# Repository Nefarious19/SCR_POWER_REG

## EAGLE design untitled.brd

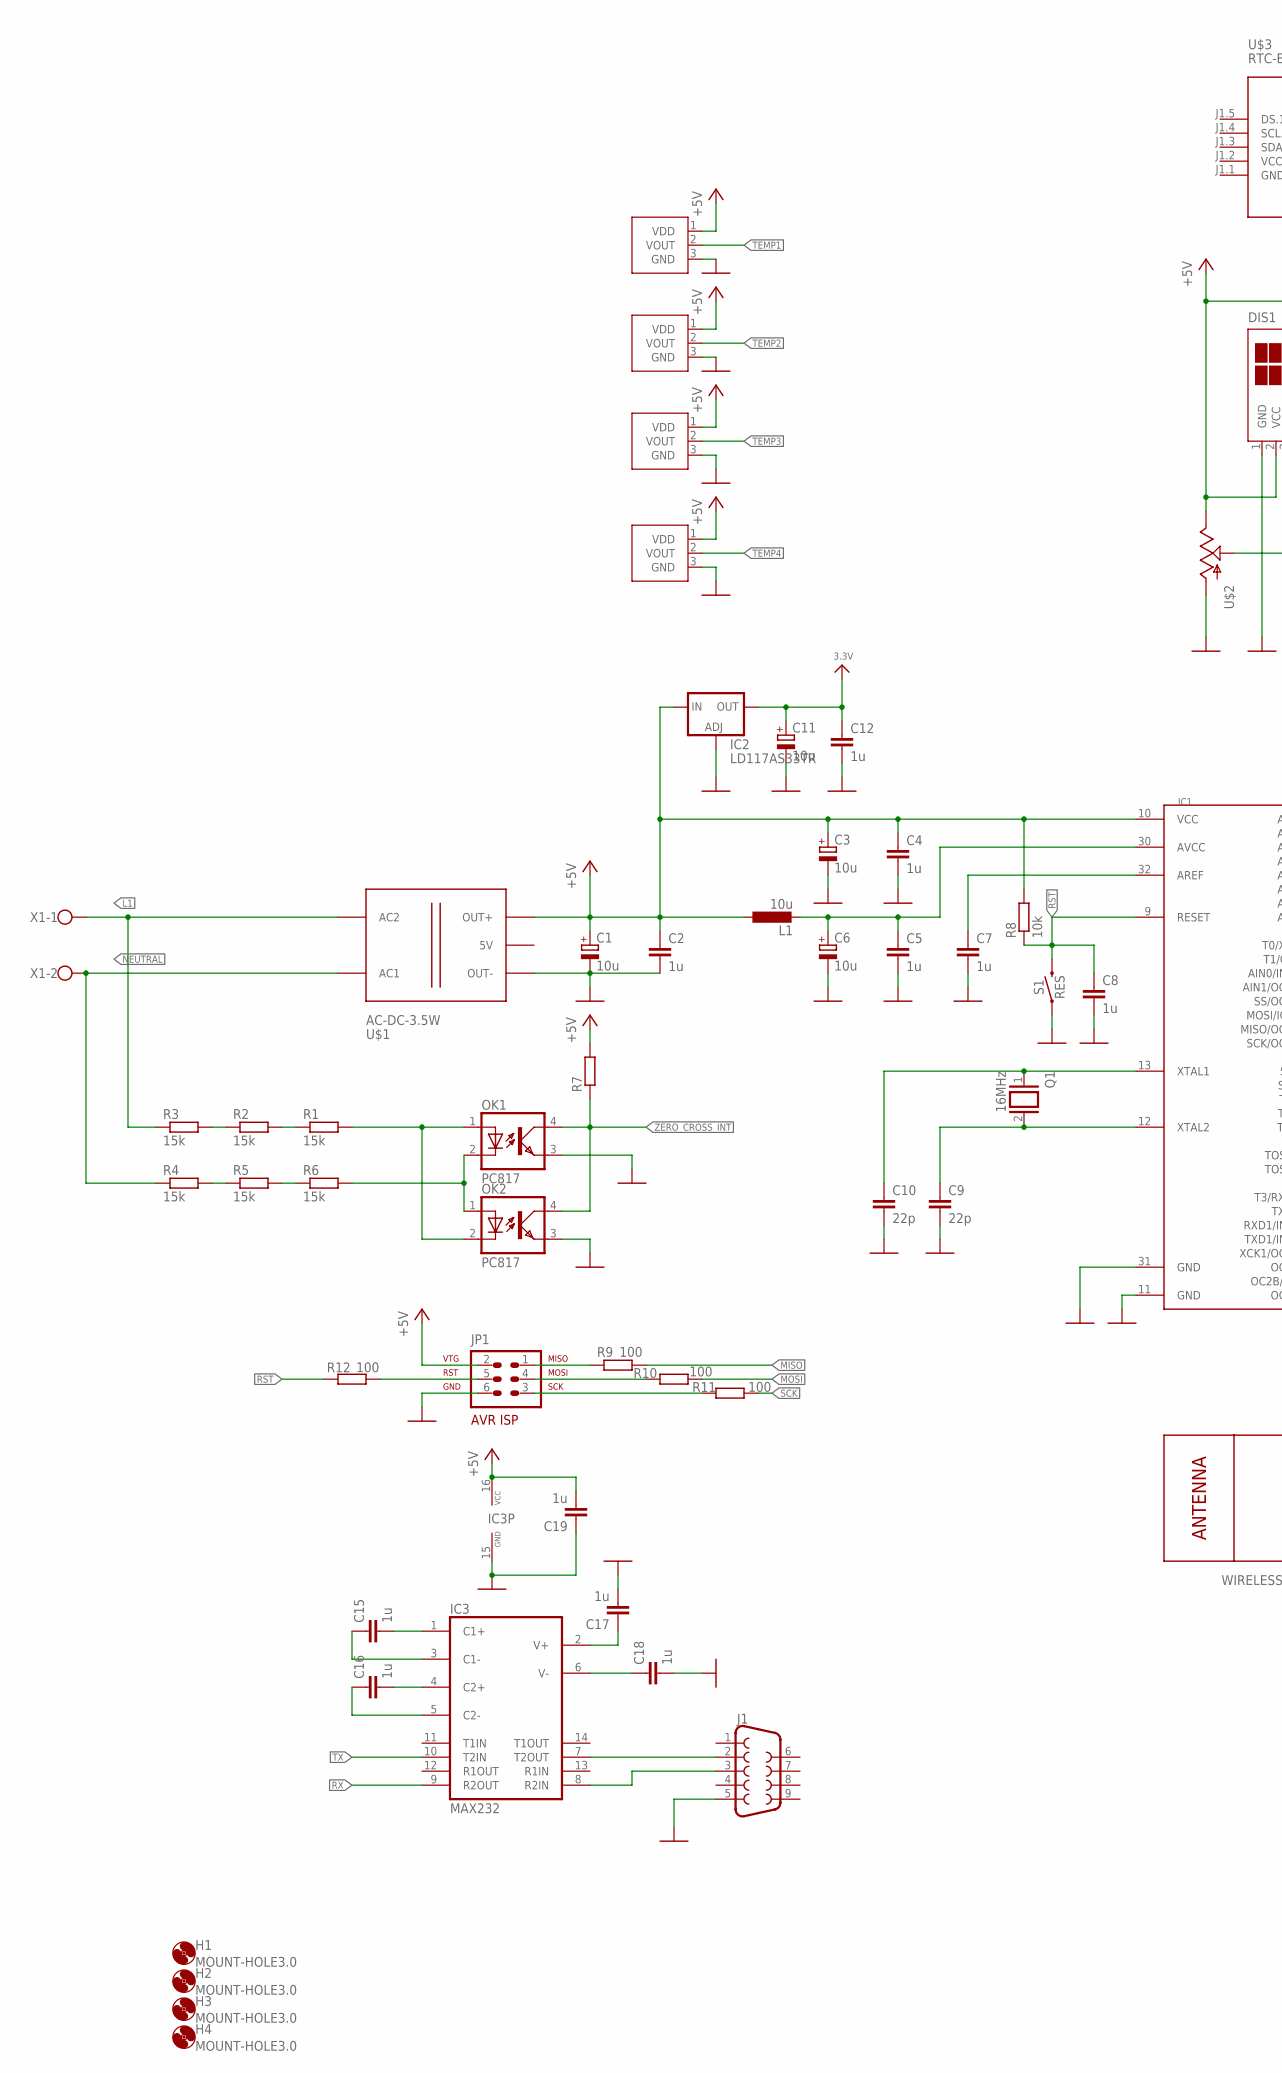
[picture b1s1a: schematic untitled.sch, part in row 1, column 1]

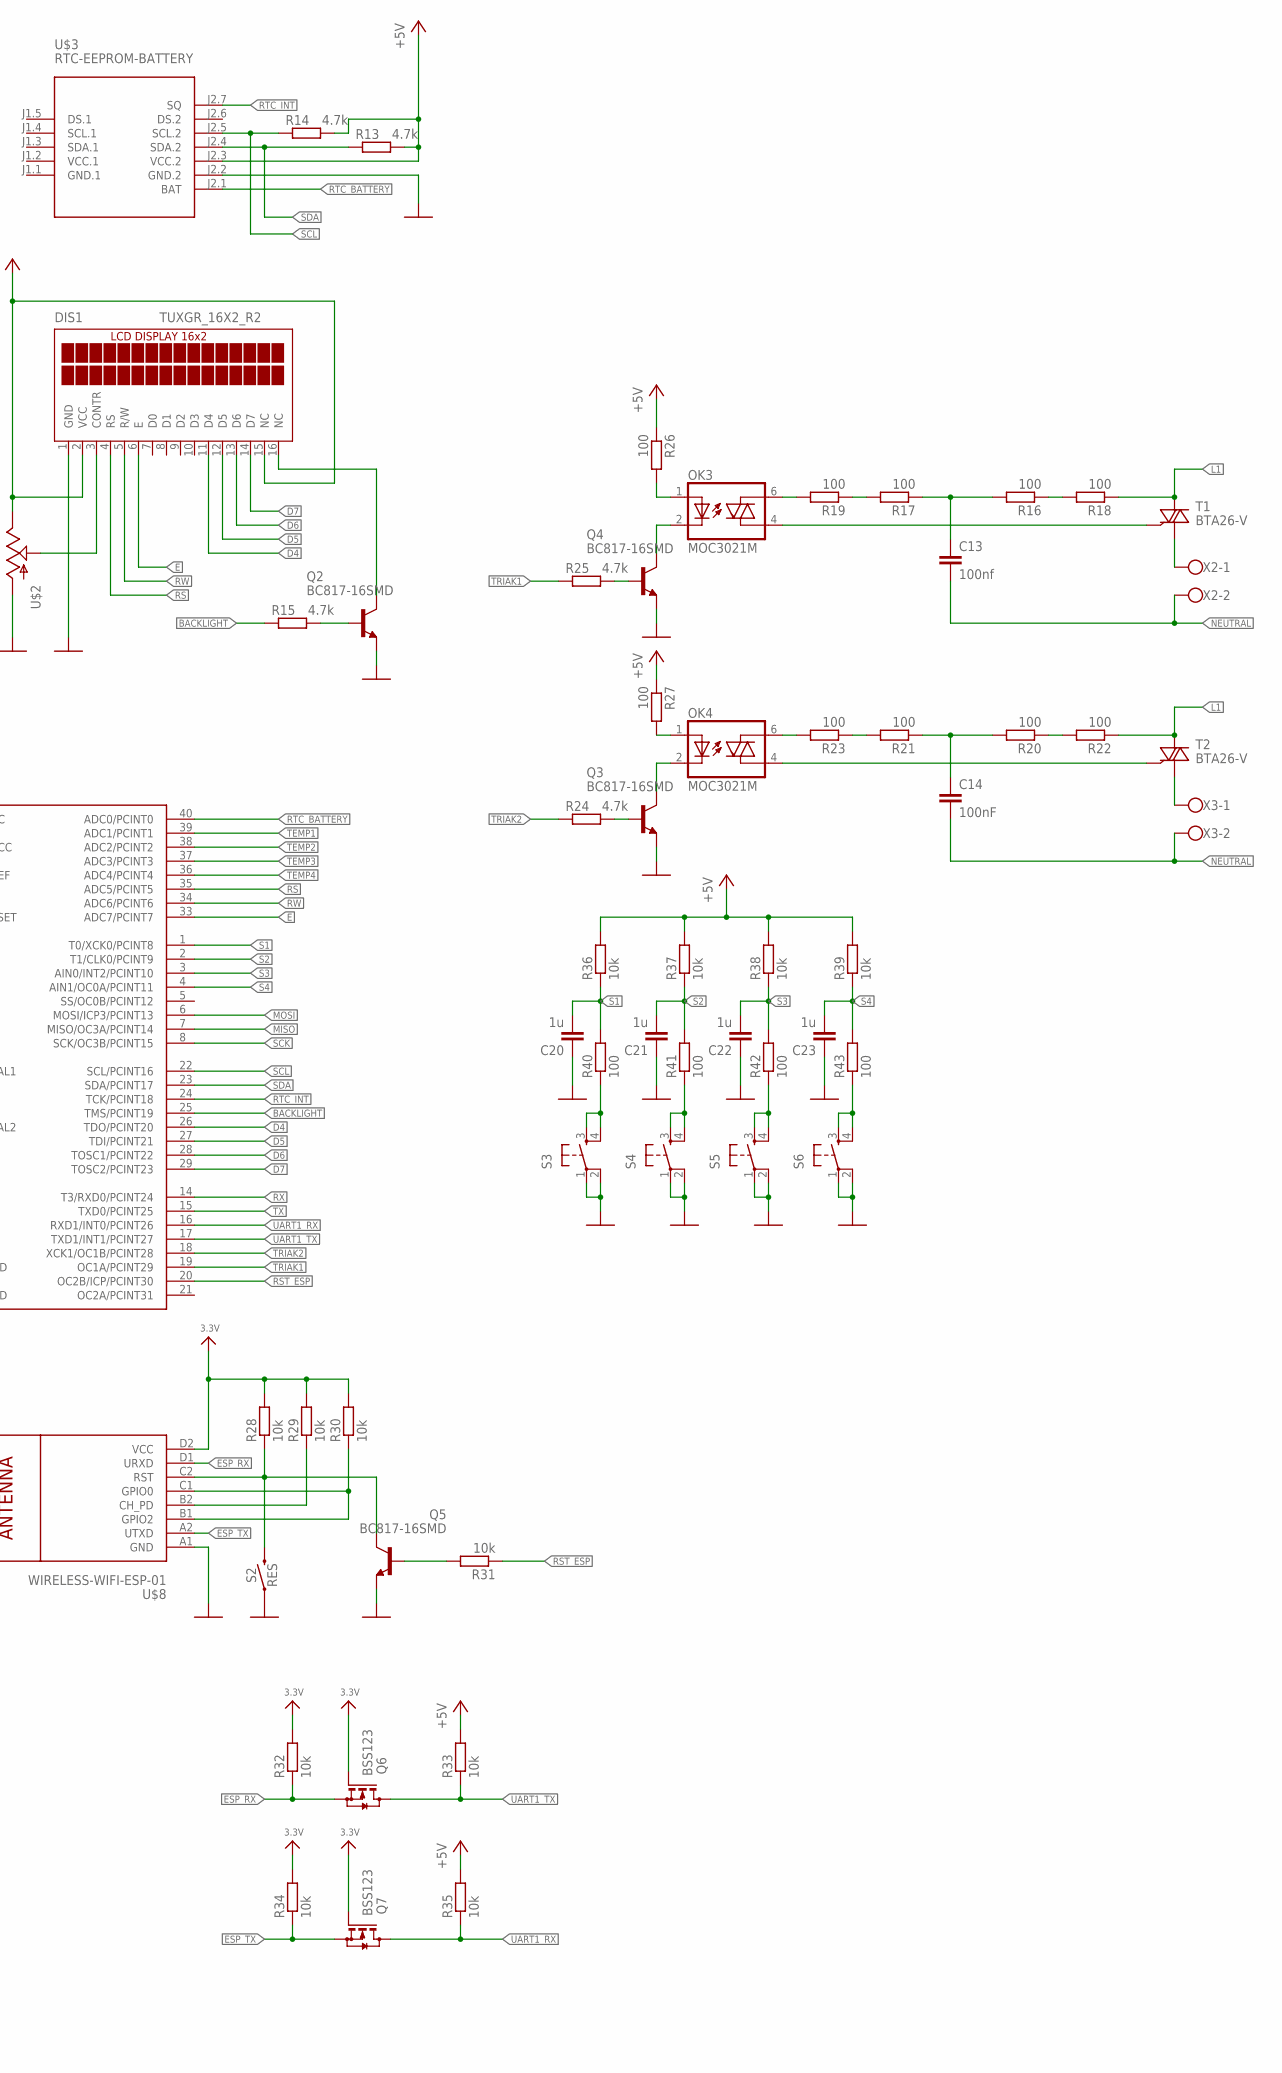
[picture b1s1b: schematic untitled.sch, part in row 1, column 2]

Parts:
C1, C3, C6, C11: 10u; 153CLV-0505
C2, C4, C5, C7, C8, C12, C15, C16, C17, C18, C19, C20, C21, C22, C23: 1u; C1206
C9, C10: 22p; C1206
C13: 100nf; C150-064X183
C14: 100nF; C150-064X183
DIS1: TUXGR_16X2_R2
H1, H2, H3, H4: MOUNT-HOLE3.0; 3,0
IC1: MEGA1284P; DIL40
IC2: LD117AS33TR; SOT223
IC3: MAX232; DIL16
J1: DB9FEMALE; DB9
JP1: AVR-ISP-6
L1: 10u; 0204/5
OK1, OK2: PC817; DIL04
OK3, OK4: MOC3021M; DIL06
Q1: 16MHz; QS
Q2, Q3, Q4, Q5: BC817-16SMD; SOT23-BEC
Q6, Q7: BSS123; SOT23
R1, R2, R3, R4, R5, R6: 15k; M1206
R7: R-EU_M1206; M1206
R8, R28, R29, R30, R31, R32, R33, R34, R35, R36, R37, R38, R39: 10k; M1206
R9, R10, R11, R12, R16, R17, R18, R19, R20, R21, R22, R23, R26, R27, R40, R41, R42, R43: 100; M1206
R13, R14, R15, R24, R25: 4.7k; M1206
S1, S2: RES; TACTILE_SWITCH_SMD_6.0X3.5MM
S3, S4, S5, S6: TAC_SWITCHPTH; TACTILE-PTH
T1, T2: BTA26-V; TOP3S-1
U$1: AC-DC-3.5W
U$2: POTTRIM; TRIM_POT
U$3: RTC-EEPROM-BATTERY
U$4, U$5, U$6, U$7: MCP970XTO; TO92
U$8: WIRELESS-WIFI-ESP-01
X1, X2, X3: AK500/2

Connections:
3.3V: C11.+, C12.1, IC2.4 (OUT), Q6.1 (G), Q7.1 (G), R28.2, R29.2, R30.2, R32.2, R34.2, U$8.D2 (VCC)
+5V: C1.+, C2.1, C3.+, C4.1, C19.2, DIS1.2 (VCC), DIS1.15 (NC), IC1.10 (VCC), IC2.3 (IN), IC3.16 (VCC), JP1.2, L1.1, R7.2, R8.2, R13.2, R14.2, R26.1, R27.1, R33.2, R35.2, R36.2, R37.2, R38.2, R39.2, U$1.J2.3 (OUT+), U$2.2 (E), U$3.J2.3 (VCC.2), U$4.1 (VDD), U$5.1 (VDD), U$6.1 (VDD), U$7.1 (VDD)
BACKLIGHT: IC1.25 (TMS/PCINT19), R15.1
D4: DIS1.11 (D4), IC1.26 (TDO/PCINT20)
D5: DIS1.12 (D5), IC1.27 (TDI/PCINT21)
D6: DIS1.13 (D6), IC1.28 (TOSC1/PCINT22)
D7: DIS1.14 (D7), IC1.29 (TOSC2/PCINT23)
E: DIS1.6 (E), IC1.33 (ADC7/PCINT7)
ESP_RST: Q5.C, R28.1, S2.2, U$8.C2 (RST)
ESP_RX: Q6.2 (S), R32.1, U$8.D1 (URXD)
ESP_TX: Q7.2 (S), R34.1, U$8.A2 (UTXD)
GND: C1.-, C2.2, C3.-, C4.2, C5.2, C6.-, C7.2, C8.2, C9.2, C10.2, C11.-, C12.2, C17.2, C18.2, C19.1, C20.1, C21.1, C22.1, C23.1, DIS1.1 (GND), IC1.11 (GND), IC1.31 (GND), IC2.1 (ADJ), IC3.15 (GND), J1.5, JP1.6, OK1.3 (EMIT), OK2.3 (EMIT), Q2.E, Q3.E, Q4.E, Q5.E, S1.1, S2.1, S3.1, S3.2, S4.1, S4.2, S5.1, S5.2, S6.1, S6.2, U$1.J2.1 (OUT-), U$2.3 (A), U$3.J2.2 (GND.2), U$4.3 (GND), U$5.3 (GND), U$6.3 (GND), U$7.3 (GND), U$8.A1 (GND)
GND.1: U$3.J1.1 (GND.1)
L1: R3.1, R18.1, R22.1, T1.A2, T2.A2, U$1.J1.2 (AC2), X1.1
MISO: IC1.7 (MISO/OC3A/PCINT14), R9.2
MOSI: IC1.6 (MOSI/ICP3/PCINT13), R10.2
unnamed: OK1.2 (C), OK2.1 (A), R6.2
unnamed: OK1.1 (A), OK2.2 (C), R1.2
unnamed: R2.1, R3.2
unnamed: R1.1, R2.2
unnamed: R5.2, R6.1
unnamed: R4.2, R5.1
unnamed: OK3.4 (A1), T1.G
unnamed: T1.A1, X2.1
unnamed: C5.1, C6.+, IC1.30 (AVCC), L1.2
unnamed: JP1.5, R12.2
unnamed: C9.1, IC1.12 (XTAL2), Q1.2
unnamed: C7.1, IC1.32 (AREF)
unnamed: C10.1, IC1.13 (XTAL1), Q1.1
unnamed: JP1.1, R9.1
unnamed: JP1.4, R10.1
unnamed: JP1.3, R11.1
unnamed: Q2.B, R15.2
unnamed: DIS1.3 (CONTR), U$2.1 (S)
unnamed: Q5.B, R31.2
unnamed: OK3.6 (A2), R19.2
unnamed: R17.2, R19.1
unnamed: C13.1, R16.2, R17.1
unnamed: R16.1, R18.2
unnamed: OK4.6 (A2), R23.2
unnamed: R21.2, R23.1
unnamed: C14.1, R20.2, R21.1
unnamed: DIS1.16 (NC), Q2.C
unnamed: R20.1, R22.2
unnamed: OK4.4 (A1), T2.G
unnamed: T2.A1, X3.1
unnamed: OK3.1 (A), R26.2
unnamed: OK3.2 (C), Q4.C
unnamed: OK4.1 (A), R27.2
unnamed: OK4.2 (C), Q3.C
unnamed: Q3.B, R24.2
unnamed: Q4.B, R25.2
unnamed: R29.1, U$8.B2 (CH_PD)
unnamed: R30.1, U$8.B1 (GPIO2), U$8.C1 (GPIO0)
unnamed: C15.2, IC3.1 (C1+)
unnamed: R40.1, S3.3, S3.4
unnamed: C16.2, IC3.4 (C2+)
unnamed: R41.1, S4.3, S4.4
unnamed: C15.1, IC3.3 (C1-)
unnamed: C16.1, IC3.5 (C2-)
unnamed: C17.1, IC3.2 (V+)
unnamed: C18.1, IC3.6 (V-)
unnamed: R42.1, S5.3, S5.4
unnamed: R43.1, S6.3, S6.4
unnamed: IC3.7 (T2OUT), J1.2
unnamed: IC3.8 (R2IN), J1.3
NEUTRAL: C13.2, C14.2, R4.1, U$1.J1.1 (AC1), X1.2, X2.2, X3.2
RS: DIS1.4 (RS), IC1.35 (ADC5/PCINT5)
RST: C8.1, IC1.9 (RESET), R8.1, R12.1, S1.2
RST_ESP: IC1.20 (OC2B/ICP/PCINT30), R31.1
RTC_BATTERY: IC1.40 (ADC0/PCINT0), U$3.J2.1 (BAT)
RTC_INT: IC1.24 (TCK/PCINT18), U$3.J2.7 (SQ)
RW: DIS1.5 (R/W), IC1.34 (ADC6/PCINT6)
RX: IC1.14 (T3/RXD0/PCINT24), IC3.9 (R2OUT)
S1: C20.2, IC1.1 (T0/XCK0/PCINT8), R36.1, R40.2
S2: C21.2, IC1.2 (T1/CLK0/PCINT9), R37.1, R41.2
S3: C22.2, IC1.3 (AIN0/INT2/PCINT10), R38.1, R42.2
S4: C23.2, IC1.4 (AIN1/OC0A/PCINT11), R39.1, R43.2
SCK: IC1.8 (SCK/OC3B/PCINT15), R11.2
SCL: IC1.22 (SCL/PCINT16), R14.1, U$3.J2.5 (SCL.2)
SDA: IC1.23 (SDA/PCINT17), R13.1, U$3.J2.4 (SDA.2)
TEMP1: IC1.39 (ADC1/PCINT1), U$7.2 (VOUT)
TEMP2: IC1.38 (ADC2/PCINT2), U$6.2 (VOUT)
TEMP3: IC1.37 (ADC3/PCINT3), U$5.2 (VOUT)
TEMP4: IC1.36 (ADC4/PCINT4), U$4.2 (VOUT)
TRIAK1: IC1.19 (OC1A/PCINT29), R25.1
TRIAK2: IC1.18 (XCK1/OC1B/PCINT28), R24.1
TX: IC1.15 (TXD0/PCINT25), IC3.10 (T2IN)
UART1_RX: IC1.16 (RXD1/INT0/PCINT26), Q7.3 (D), R35.1
UART1_TX: IC1.17 (TXD1/INT1/PCINT27), Q6.3 (D), R33.1
VCC.1: U$3.J1.2 (VCC.1)
ZERO_CROSS_INT: OK1.4 (COL), OK2.4 (COL), R7.1

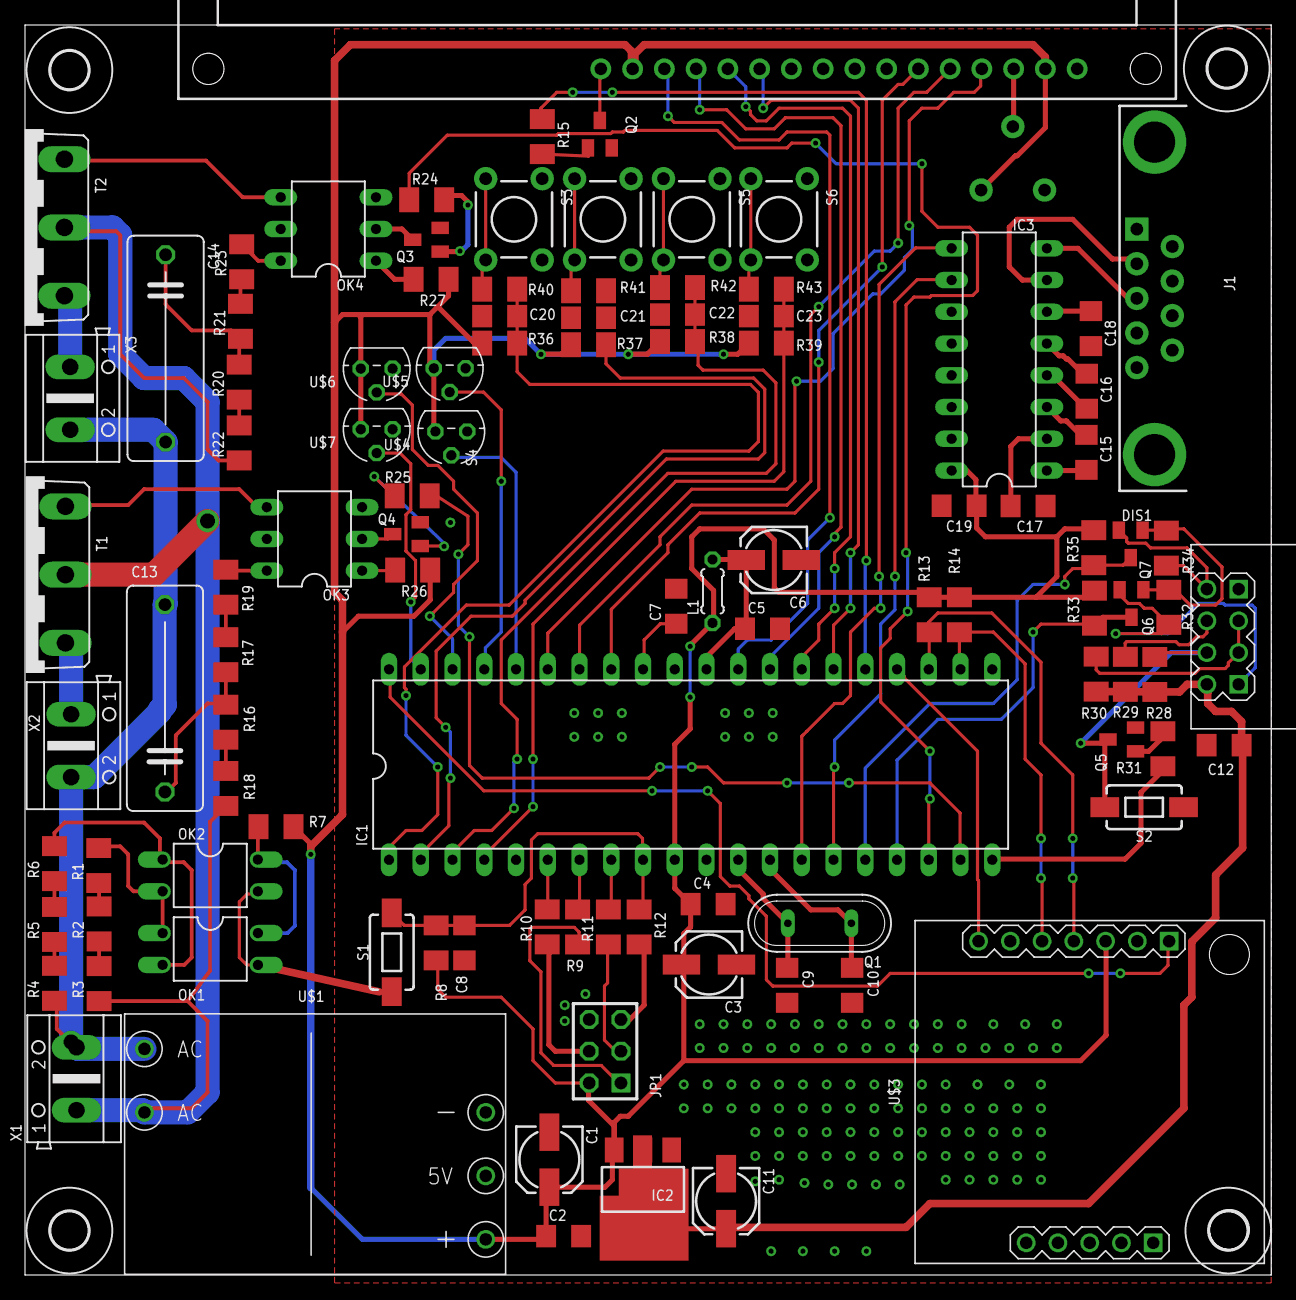
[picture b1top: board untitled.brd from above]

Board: 2 copper layers, 99.7 x 100.0 mm, 107 parts (0 on the bottom side), 90 nets.

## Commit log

2018-01-09 version beta

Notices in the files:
parts and their libraries:
diy-modules: Released under the Creative Commons Attribution 4.0 International License: http://creativecommons.org/licenses/by/4.0
SparkFun-Switches: Licensing: Creative Commons ShareAlike 4.0 International - https://creativecommons.org/licenses/by-sa/4.0
